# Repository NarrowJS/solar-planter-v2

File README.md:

# Solar Planter V2
Integrates temperature, humidity, and soil moisture sensing into a single discrete plant pot and notifies you of the plant's health using LEDs and push notifications via IOT. The pot features a solar panel on the side to slowly recharge the internal battery, removing the need for recharging the device manually.
### Features
- Zigbee and Matter connectivity for low power wireless communication
- RGB Leds for notification
- Easily removable plant pot via magnets for a modular design
- Removable temperature and humidity sensor module

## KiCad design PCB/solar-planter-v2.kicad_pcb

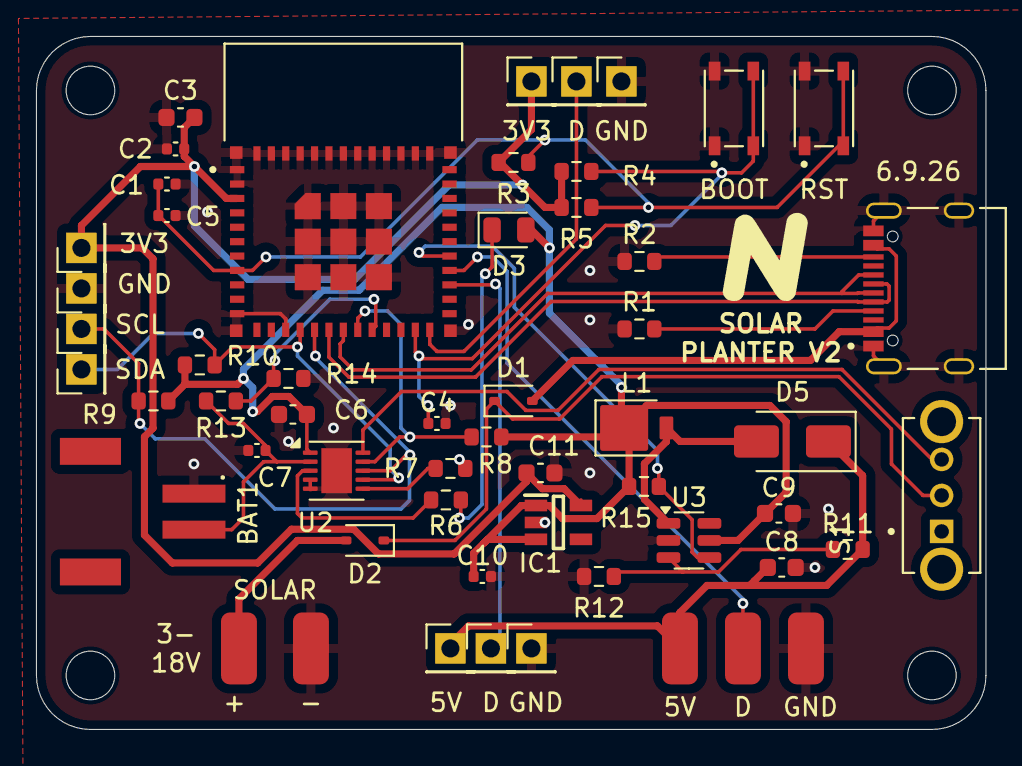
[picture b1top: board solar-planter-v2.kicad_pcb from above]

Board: 2 copper layers, 52.8 x 38.5 mm, 59 parts (0 on the bottom side), 28 nets.

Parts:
3V3: MOISTURE_VCC; PinHeader_1x01_P2.54mm_Vertical
3V3#2: 3V3; PinHeader_1x01_P2.54mm_Vertical
5V: TEMP_VCC; PinHeader_1x01_P2.54mm_Vertical
5V#2: LED_VCC; SolderWirePad_1x01_SMD_1x2mm
+: +SOLAR; SolderWirePad_1x01_SMD_1x2mm
-: SOLAR-; SolderWirePad_1x01_SMD_1x2mm
BAT1: S2B-PH-SM4-TB; JST_S2B-PH-SM4-TB
BOOT: PTS810_SJM_250_SMTR_LFS; SW_PTS810_SJM_250_SMTR_LFS
C1, C2, C4, C5: 100nF; C_0402_1005Metric
C3, C6, C11: 10uF; C_0603_1608Metric
C7, C10: 1uF; C_0402_1005Metric
C8, C9: 22uF; C_0603_1608Metric
D: MOISTURE_DATA; PinHeader_1x01_P2.54mm_Vertical
D1, D2: 1N5819WS; D_SOD-323
D3: CHARGE LED; LED_0805_2012Metric
D5: SS34; D_SMA
D#2: LED_DATA; SolderWirePad_1x01_SMD_1x2mm
D#3: TEMP_DATA; PinHeader_1x01_P2.54mm_Vertical
GND: LED_GND; SolderWirePad_1x01_SMD_1x2mm
GND#2: TEMP_GND; PinHeader_1x01_P2.54mm_Vertical
GND#3: MOISTURE_GND; PinHeader_1x01_P2.54mm_Vertical
GND#4: LED_GND; PinHeader_1x01_P2.54mm_Vertical
H1, H2, H3, H4: MountingHole; MountingHole_2.7mm_M2.5
IC1: RT9080-33GJ5; SOT94P280X100-5N
J1: TYPE-C-31-M-12; HRO_TYPE-C-31-M-12
L1: CD32; D_SMP_DO-220AA
R1, R2: 5k1; R_0603_1608Metric
R3, R4, R5, R7, R8, R9, R10, R15: 10k; R_0603_1608Metric
R6, R12: 1k; R_0603_1608Metric
R11: 7K5; R_0603_1608Metric
R13: 27k; R_0603_1608Metric
R14: 100k; R_0603_1608Metric
RST: PTS810_SJM_250_SMTR_LFS; SW_PTS810_SJM_250_SMTR_LFS
S1: EG1247; SW_EG1247
SCL: SCL; PinHeader_1x01_P2.54mm_Vertical
SDA: SDA; PinHeader_1x01_P2.54mm_Vertical
U1: ESP32-C6-MINI-1-H4; XCVR_ESP32-C6-MINI-1-H4
U2: PQ25186DLHR; DFN-10-1EP_3x3mm_P0.5mm_EP1.7x2.5mm
U3: MT3608; SOT-23-6

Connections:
+3V3: 3V3.1, 3V3#2.1, C2.1, C3.1, C11.1, IC1.5 (VOUT), R3.1, R4.1, R5.1, U1.3 (3V3)
+5V: 5V.1, 5V#2.1, C8.1, D5.1 (K), R11.2
+BAT: BAT1.2, C7.1, R13.1, U2.2 (BAT)
+IN: S1.3, U2.10 (IN)
+SOLAR: +.1, D2.2 (A)
+SYS: C6.1, C9.1, C10.1, D3.2 (A), IC1.1 (VIN), IC1.3 (EN), L1.1, R8.2, R9.2, R10.2, R15.1, U2.1 (SYS), U3.5 (IN)
+VBUS: D1.2 (A), J1.A4_B9 (VBUS), J1.B4_A9 (VBUS)
BAT_LVL: R13.2, R14.1, U1.20 (IO15)
CHIP_PU: C1.1, C5.1, R3.2, R5.2, RST.3, RST.4, U1.8 (EN)
GND: -.1, BAT1.1, BOOT.1, BOOT.2, C1.2, C2.2, C3.2, C4.2, C5.2, C6.2, C7.2, C8.2, C9.2, C10.2, C11.2, GND.1, GND#2.1, GND#3.1, GND#4.1, IC1.2 (GND), J1.A1_B12 (GND), J1.B1_A12 (GND), J1.S1 (SHIELD), J1.S2 (SHIELD), J1.S3 (SHIELD), J1.S4 (SHIELD), R1.1, R2.1, R7.2, R12.1, R14.2, RST.1, RST.2, U1.1 (GND1), U1.2 (GND1), U1.11 (GND1), U1.14 (GND1), U1.36 (GND1), U1.37 (GND1), U1.38 (GND1), U1.39 (GND1), U1.40 (GND1), U1.41 (GND1), U1.42 (GND1), U1.43 (GND1), U1.44 (GND1), U1.45 (GND1), U1.46 (GND1), U1.47 (GND2), U1.48 (GND2), U1.49_1 (GND2), U1.49_2 (GND2), U1.49_3 (GND2), U1.49_4 (GND2), U1.49_5 (GND2), U1.49_6 (GND2), U1.49_7 (GND2), U1.49_8 (GND2), U1.49_9 (GND2), U1.50 (GND2), U1.51 (GND2), U1.52 (GND2), U1.53 (GND2), U2.4 (/CE), U2.5 (GND), U2.11 (EPAD), U3.2 (GND)
GPIO9: BOOT.3, BOOT.4, C4.1, R4.2, U1.23 (IO9)
GPIO14: R8.1, U1.19 (IO14), U2.9 (/INT)
GPIO18: D.1, U1.24 (IO18)
GPIO21: D#3.1, U1.27 (IO21)
GPIO22: D#2.1, U1.28 (IO22)
GPIO23: R15.2, U1.29 (IO23), U3.4 (EN)
unnamed: D1.1 (K), D2.1 (K), S1.2
unnamed: D3.1 (K), R6.1
unnamed: D5.2 (A), L1.2, U3.1 (SW)
unnamed: J1.A5 (CC1), R1.2
unnamed: J1.B5 (CC2), R2.2
unnamed: R7.1, U2.6 (TS/MR)
unnamed: R6.2, U2.3 (/PG/GPO)
unnamed: R11.1, R12.2, U3.3 (FB)
SCL: R9.1, SCL.1, U1.16 (IO7), U2.8 (SCL)
SDA: R10.1, SDA.1, U1.15 (IO6), U2.7 (SDA)
USB_D+: J1.A6 (DP1), J1.B6 (DP2), U1.18 (IO13)
USB_D-: J1.A7 (DN1), J1.B7 (DN2), U1.17 (IO12)

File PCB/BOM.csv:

Id;Designator;Footprint;Quantity;Designation;Part #;Link
1;S1;SW_EG1247;1;EG1247;C431548;https://www.lcsc.com/product-detail/C431548.html
2;D3;LED_0805_2012Metric;1;CHARGE LED;C19273154;https://www.lcsc.com/product-detail/C19273154.html
3;C4,C5,C1,C2;C_0402_1005Metric;4;100nF;C60474;https://www.lcsc.com/product-detail/C60474.html
4;U1;XCVR_ESP32-C6-MINI-1-H4;1;ESP32-C6-MINI-1-H4;C6553337;https://www.lcsc.com/product-detail/C6553337.html
5;3V3;PinHeader_1x01_P2.54mm_Vertical;1;MOISTURE_VCC;;
6;GND;SolderWirePad_1x01_SMD_1x2mm;1;LED_GND;;
7;R3,R4,R5,R10,R15,R8,R9,R7;R_0603_1608Metric;8;10k;C95204;https://www.lcsc.com/product-detail/C95204.html
8;C8,C9;C_0603_1608Metric;2;22uF;C86295;https://www.lcsc.com/product-detail/C86295.html
9;R6,R12;R_0603_1608Metric;2;1k;C5362357;https://www.lcsc.com/product-detail/C5362357.html
10;R2,R1;R_0603_1608Metric;2;5k1;C2907044;https://www.lcsc.com/product-detail/C2907044.html
11;D;PinHeader_1x01_P2.54mm_Vertical;1;MOISTURE_DATA;;
12;5V;PinHeader_1x01_P2.54mm_Vertical;1;TEMP_VCC;;
13;BOOT,RST;SW_PTS810_SJM_250_SMTR_LFS;2;PTS810_SJM_250_SMTR_LFS;C116501;https://www.lcsc.com/product-detail/C116501.html
14;C6,C11,C3;C_0603_1608Metric;3;10uF;C19702;https://www.lcsc.com/product-detail/C19702.html
15;D5;D_SMA;1;SS34;C908680;https://www.lcsc.com/product-detail/C908680.html
16;GND;PinHeader_1x01_P2.54mm_Vertical;1;TEMP_GND;;
17;U3;SOT-23-6;1;MT3608;C84817;https://www.lcsc.com/product-detail/C84817.html
18;C7,C10;C_0402_1005Metric;2;1uF;C29266;https://www.lcsc.com/product-detail/C29266.html
19;IC1;SOT94P280X100-5N;1;RT9080-33GJ5;C841192;https://www.lcsc.com/product-detail/C841192.html
20;+ -;JST_S2B-PH-SM4-TB;1;S2B-PH-SM4-TB;C295747;https://www.lcsc.com/product-detail/C295747.html
21;D2,D1;D_SOD-323;2;1N5819WS;C191023;https://www.lcsc.com/product-detail/C191023.html
22;J1;HRO_TYPE-C-31-M-12;1;TYPE-C-31-M-12;C165948;https://www.lcsc.com/product-detail/C165948.html
23;+;SolderWirePad_1x01_SMD_1x2mm;1;+SOLAR;;
24;3V3;PinHeader_1x01_P2.54mm_Vertical;1;3V3;;
25;GND;PinHeader_1x01_P2.54mm_Vertical;1;MOISTURE_GND;;
26;SDA;PinHeader_1x01_P2.54mm_Vertical;1;SDA;;
27;L1;D_SMP_DO-220AA;1;CD32;C41408473;https://www.lcsc.com/product-detail/C41408473.html
28;GND;PinHeader_1x01_P2.54mm_Vertical;1;LED_GND;;
29;R11;R_0603_1608Metric;1;7K5;C23234;https://www.lcsc.com/product-detail/C23234.html
30;D;SolderWirePad_1x01_SMD_1x2mm;1;LED_DATA;;
31;5V;SolderWirePad_1x01_SMD_1x2mm;1;LED_VCC;;
32;SCL;PinHeader_1x01_P2.54mm_Vertical;1;SCL;;
33;-;SolderWirePad_1x01_SMD_1x2mm;1;SOLAR-;;
34;R14;R_0603_1608Metric;1;100k;C14675;https://www.lcsc.com/product-detail/C14675.html
35;U2;DFN-10-1EP_3x3mm_P0.5mm_EP1.7x2.5mm;1;PQ25186DLHR;C44639442;https://www.lcsc.com/product-detail/C44639442.html
36;D;PinHeader_1x01_P2.54mm_Vertical;1;TEMP_DATA;;
37;R13;R_0603_1608Metric;1;27k;C22967;https://www.lcsc.com/product-detail/C22967.html

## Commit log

2026-05-17 initial
2026-05-17 add time
2026-05-17 fix time
2026-05-19 '5-18'
2026-05-20 5/19
2026-05-21 5/20
2026-05-21 5-20 2
2026-05-21 fix date
2026-05-21 fix formatting
2026-05-22 5-21
2026-06-08 route front layer
2026-06-09 finished PCB design
2026-06-09 fix image
2026-06-09 fix trace widths
2026-06-09 Add removable pot enclosure
2026-06-10 polish 3d model
2026-06-11 add files
2026-06-11 Add initial project description and features to README
2026-06-11 Update README with improved feature details
    Enhanced feature descriptions for clarity.
